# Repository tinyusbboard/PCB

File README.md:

PCB
===

This is the tinyUSBboard Rev.4 SMT single board PCB

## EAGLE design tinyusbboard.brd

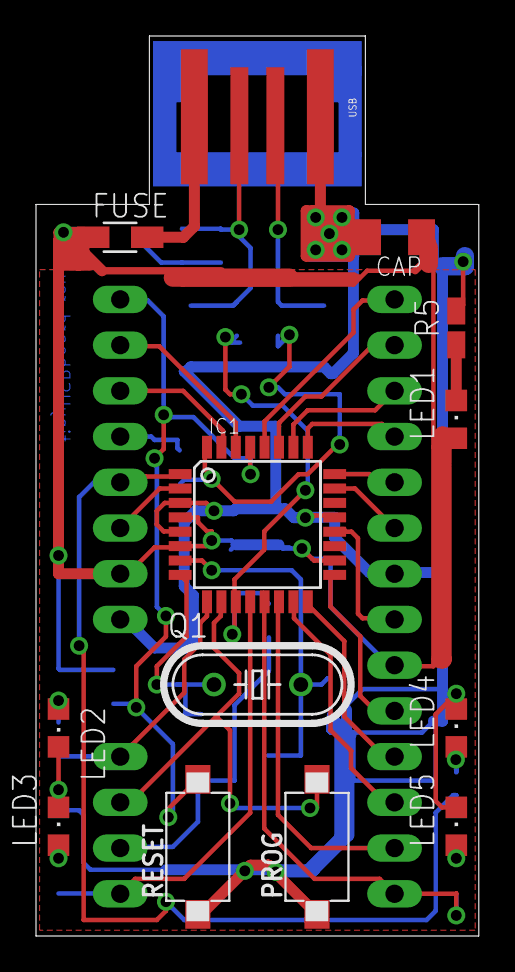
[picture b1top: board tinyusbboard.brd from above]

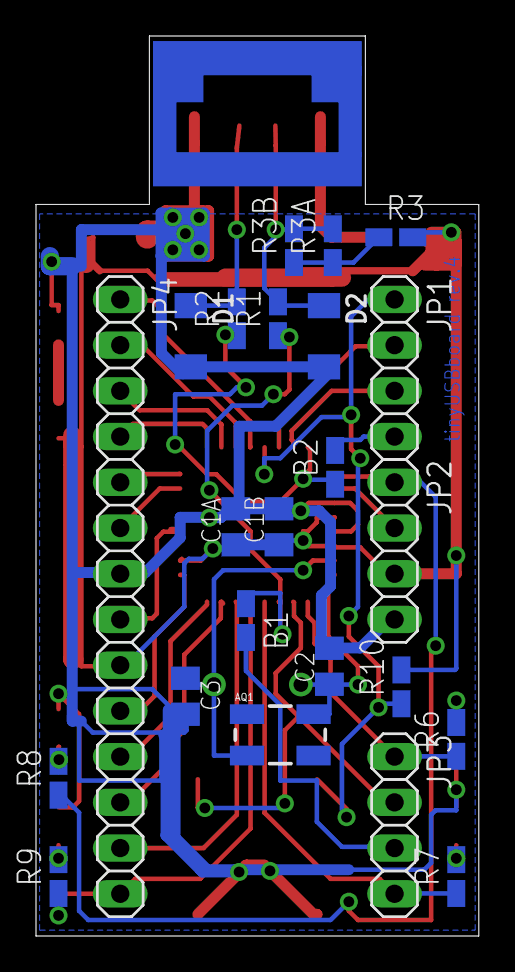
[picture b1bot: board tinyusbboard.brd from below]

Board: 2 copper layers, 24.6 x 50.0 mm, 36 parts (23 on the bottom side), 37 nets.

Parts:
AQ1: 16MHz; CRYSTAL-SMD-5X3
B1, B2: 0; R0805W
C1A, C1B: 100nF; C0805K
C2, C3: 18pF; C0805K
CAP: 4.7uF; C1206K
D1, D2: 3V6; SOD80
FUSE: 0; R1206W
IC1: MEGA8-AI; TQFP32-08
JP1: PDA; 1X04
JP2: PDB; 1X04
JP3: PDC; 1X04
JP4: PBPC; 1X14
LED1: green; CHIPLED_0805
LED2, LED3, LED4, LED5: red; CHIPLED_0805
PROG: KSS-2EG4430
Q1: 16MHz; HC49/S
R1, R2: 68R; R0805W
R3, R3A, R3B, R6, R7, R8, R9: 1k; R0805W
R5: 10k or 1k; R0805W
R10: 10k; R0805W
RESET: KSS-2EG4430
USB: USBPCB; USB-A-PCB

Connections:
+5V: FUSE.1, USB.5V
AREF: IC1.20, JP4.8
GND: C1A.2, C1B.2, C2.2, C3.2, CAP.2, D1.A, D2.A, IC1.3, IC1.5, IC1.21, JP2.4, JP4.7, LED2.C, LED3.C, LED4.C, LED5.C, PROG.1, R5.2, RESET.1, USB.GND
unnamed: R3.1, R3A.1, R3B.1
unnamed: D1.C, R2.2, USB.USB_P
unnamed: AQ1.1, C3.1, IC1.7, Q1.1
unnamed: AQ1.3, C2.1, IC1.8, Q1.2
unnamed: B2.2, JP1.4
unnamed: D2.C, R1.2, R3A.2, R3B.2, USB.USB_M
unnamed: B1.2, JP3.3
unnamed: LED1.C, R5.1
unnamed: LED2.A, R6.2
unnamed: LED3.A, R7.2
unnamed: LED4.A, R8.2
unnamed: LED5.A, R9.2
PB0: IC1.12, JP3.4, R7.1
PB1: IC1.13, JP4.14, R9.1
PB2: IC1.14, JP4.13
PB3: IC1.15, JP4.12
PB4: IC1.16, JP4.11
PB5: IC1.17, JP4.10
PC0: IC1.23, JP4.6
PC1: IC1.24, JP4.5
PC2: IC1.25, JP4.4
PC3: IC1.26, JP4.3
PC4: IC1.27, JP4.2
PC5: IC1.28, JP4.1
PD0: IC1.30, JP1.2
PD1: IC1.31, JP1.3
PD2: B2.1, IC1.32, R2.1
PD3: IC1.1, JP2.1, R8.1
PD4: IC1.2, JP2.2
PD5: IC1.9, JP3.1, R6.1
PD6: IC1.10, JP3.2, PROG.2
PD7: B1.1, IC1.11, R1.1
RESET: IC1.29, JP1.1, R10.1, RESET.2
VCC: C1A.1, C1B.1, CAP.1, FUSE.2, IC1.4, IC1.6, IC1.18, JP2.3, JP4.9, LED1.A, R3.2, R10.2

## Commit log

2014-12-14 Add Eagle 7.1 files of tinyUSBboard SMT Rev.4
2015-07-23 More conventional schematic and plus lower capacities to confirm to the USB maximum

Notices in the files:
parts and their libraries:
SparkFun: Licensing: CC v3.0 Share-Alike You are welcome to use this library for commercial purposes.
